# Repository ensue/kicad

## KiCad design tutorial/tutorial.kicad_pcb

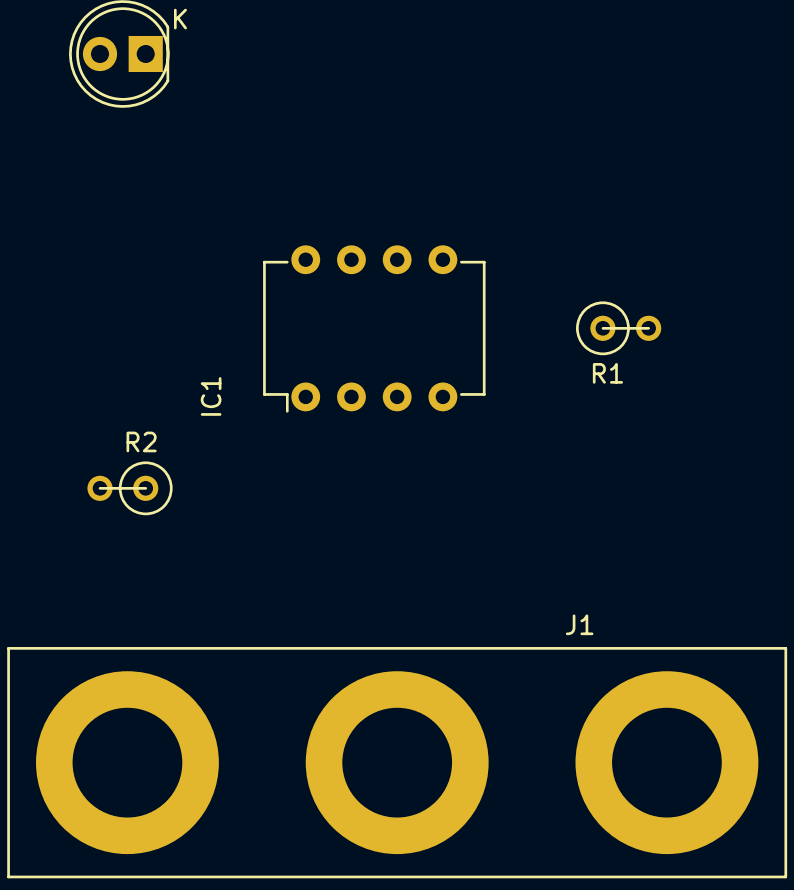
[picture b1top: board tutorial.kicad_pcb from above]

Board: 2 copper layers, 5 parts (0 on the bottom side), 6 nets, no tracks yet.

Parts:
D1: LED; LED-5MM
IC1: PIC12C508A-I/SN; DIP-8_W7.62mm
J1: MYCONN3; Banana_Jack_3Pin
R1: 100; R1
R2: 1 k; R1

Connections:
/INPUT: IC1.6, R1.1
/INPUTtoR.: J1.2, R1.2
/uCtoLED.: D1.1, IC1.7
GND: IC1.8, J1.3
unnamed: D1.2, R2.2
VCC: IC1.1, J1.1, R2.1

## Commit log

2016-08-25 pierwszy commit
2016-08-25 zmieniony tekst
2016-08-25 zmieniony tekst v2
2016-08-25 nowy plik
2016-08-25 nowy 3 plik
2016-08-25 pliki do branch pomysl
2016-08-25 pierwszy public commit
2016-08-25 elo dziuk
2016-08-26 text5
2016-08-26 text6
2016-08-26 text7
2016-08-30 kicad tutorial
